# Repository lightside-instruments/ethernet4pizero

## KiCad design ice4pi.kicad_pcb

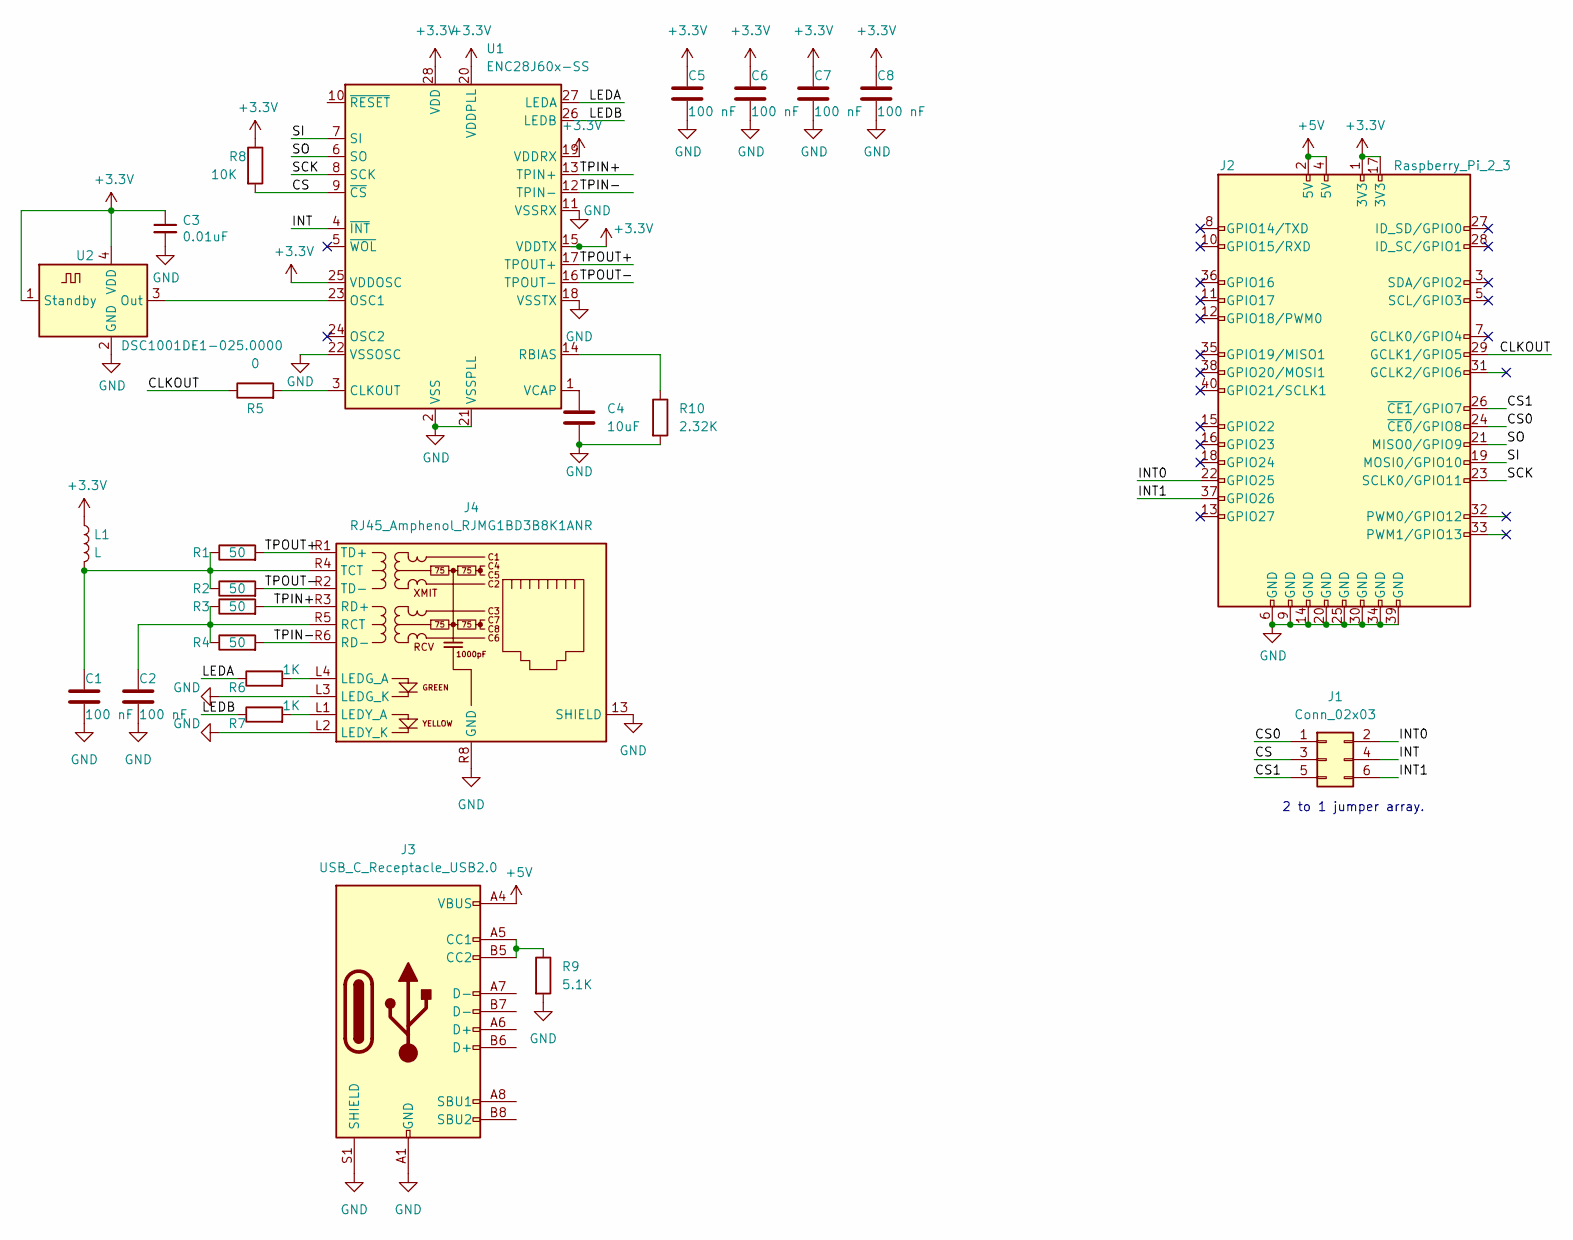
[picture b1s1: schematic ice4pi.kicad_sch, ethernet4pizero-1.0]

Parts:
C1, C2, C5, C6, C7, C8: 100 nF; C_0402_1005Metric
C3: 0.01uF; C_0402_1005Metric
C4: 10uF; C_0402_1005Metric
J1: Conn_02x03; PinHeader_2x03_P2.54mm_Vertical
J2: Raspberry_Pi_2_3; PinSocket_2x20_P2.54mm_Vertical_1_04mm
J3: USB_C_Receptacle_USB2.0; USB_C_Receptacle_GCT_USB4105-xx-A_16P_TopMnt_Horizontal
J4: RJ45_Amphenol_RJMG1BD3B8K1ANR
L1: L; L_1210_3225Metric
R1, R2, R3, R4: 50; R_0402_1005Metric
R5: 0; R_0402_1005Metric
R6, R7: 1K; R_0402_1005Metric
R8: 10K; C_0402_1005Metric
R9: 5.1K; R_0402_1005Metric
R10: 2.32K; R_0402_1005Metric
U1: ENC28J60x-SS; SSOP-28_5.3x10.2mm_P0.65mm
U2: DSC1001DE1-025.0000; Oscillator_SMD_Abracon_ASDMB-4Pin_2.5x2.0mm

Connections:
+3.3V: C3.1, C5.1, C6.1, C7.1, C8.1, J2.1 (3V3), J2.17 (3V3), L1.1, R8.1, U1.15 (VDDTX), U1.19 (VDDRX), U1.20 (VDDPLL), U1.25 (VDDOSC), U1.28 (VDD), U2.1 (Standby), U2.4 (VDD)
+5V: J2.2 (5V), J2.4 (5V), J3.A4 (VBUS), J3.A9 (VBUS), J3.B4 (VBUS), J3.B9 (VBUS)
/CLKOUT: J2.29 (GCLK1/GPIO5), R5.1
/CS: J1.3, R8.2, U1.9 (~CS)
/CS0: J1.1, J2.24 (~CE0/GPIO8)
/CS1: J1.5, J2.26 (~CE1/GPIO7)
/INT: J1.4, U1.4 (~INT)
/INT0: J1.2, J2.22 (GPIO25)
/INT1: J1.6, J2.37 (GPIO26)
/LEDA: R6.1, U1.27 (LEDA)
/LEDB: R7.1, U1.26 (LEDB)
/SCK: J2.23 (SCLK0/GPIO11), U1.8 (SCK)
/SI: J2.19 (MOSI0/GPIO10), U1.7 (SI)
/SO: J2.21 (MISO0/GPIO9), U1.6 (SO)
/TPIN+: J4.R3 (RD+), R3.2, U1.13 (TPIN+)
/TPIN-: J4.R6 (RD-), R4.2, U1.12 (TPIN-)
/TPOUT+: J4.R1 (TD+), R1.2, U1.17 (TPOUT+)
/TPOUT-: J4.R2 (TD-), R2.2, U1.16 (TPOUT-)
GND: C1.2, C2.2, C3.2, C4.2, C5.2, C6.2, C7.2, C8.2, J2.6 (GND), J2.9 (GND), J2.14 (GND), J2.20 (GND), J2.25 (GND), J2.30 (GND), J2.34 (GND), J2.39 (GND), J3.A1 (GND), J3.A12 (GND), J3.B1 (GND), J3.B12 (GND), J3.S1 (SHIELD), J4.13 (SHIELD), J4.L2 (LEDY_K), J4.L3 (LEDG_K), J4.R8 (GND), R9.2, R10.2, U1.2 (VSS), U1.11 (VSSRX), U1.18 (VSSTX), U1.21 (VSSPLL), U1.22 (VSSOSC), U2.2 (GND)
unnamed: C1.1, J4.R4 (TCT), L1.2, R1.1, R2.1
unnamed: C2.1, J4.R5 (RCT), R3.1, R4.1
unnamed: C4.1, U1.1 (VCAP)
unnamed: J3.A5 (CC1), J3.B5 (CC2), R9.1
unnamed: J4.L1 (LEDY_A), R7.2
unnamed: J4.L4 (LEDG_A), R6.2
unnamed: R10.1, U1.14 (RBIAS)
unnamed: R5.2, U1.3 (CLKOUT)
unnamed: U1.23 (OSC1), U2.3 (Out)

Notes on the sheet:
2 to 1 jumper array.

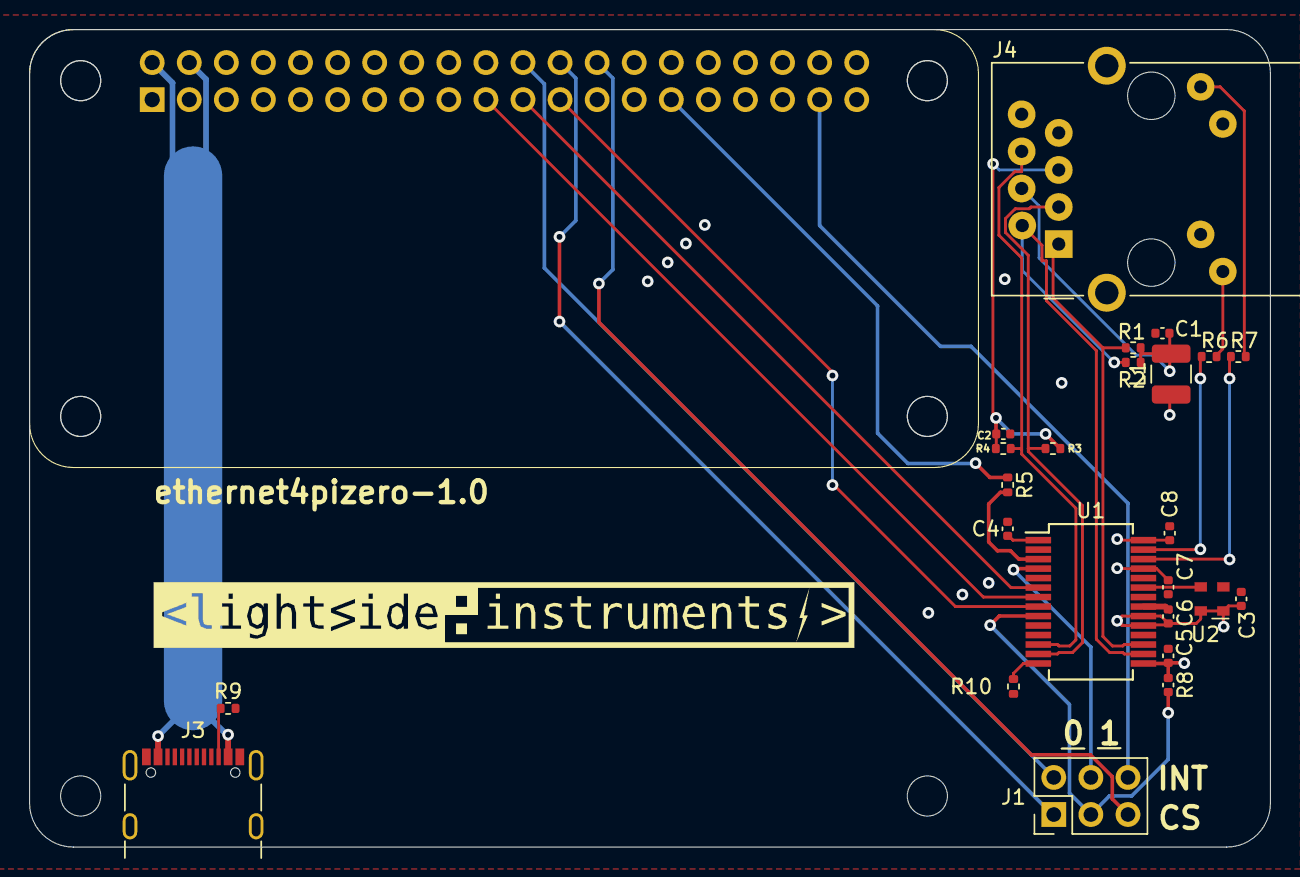
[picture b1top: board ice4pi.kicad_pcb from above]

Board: 4 copper layers, 85.0 x 56.0 mm, 26 parts (1 on the bottom side), 28 nets.

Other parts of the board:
svg2mod: G***; lsi-logo-48mm

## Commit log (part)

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2024-08-09 Release etherenet4pizero-1.0-1
